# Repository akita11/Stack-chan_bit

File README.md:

# Stack-chan_bit

[ｽﾀｯｸﾁｬﾝ](https://protopedia.net/prototype/2345Stack-chan)に[micro:bit](https://www.switch-science.com/products/7952)を差し込んで制御するボードです。micro:bitのプログラミングでｽﾀｯｸﾁｬﾝを動かすことができます。

## 使用例

micro:bit側のプログラム（m-asaoka-fap氏作成の[カスタムブロック](https://github.com/m-asaoka-fap/stackchanbit_2)あり）から、ｽﾀｯｸﾁｬﾝを制御できます。→[使用例](https://twitter.com/akita11/status/1656496746321842176)

## 作り方

### 用意するもの

- M5Stack (BasicまたはCore2がオススメ)
- [Stack-chan_Takao_Base](https://github.com/akita11/Stack-chan_Takao_Base)とそれで用いるもの（サーボモータ2個、Groveケーブル、ネジ等、筐体(shell部以外)）※顔部分のM5Stack本体との固定には、BasicではM3x15mm、Core2ではM3x20mmのネジを2本使います
- shell部の筐体(Stack-chan_bit_shell.stlを3Dプリントしたもの): [タカオ版筐体](https://github.com/meganetaaan/stack-chan/tree/dev/v1.0/case/contributed/mongonta_case_for_SG90_and_M5GoBottomBoard/case_for_SG90andM5GoBottomBoard)内の”shell_SG90_basicgraybottom_v1.0.stl"を元に改変

### 組み立て

M5Stackに専用プログラム（FW_PIO/以下。PlatformIO用）を書き込みます。

M5Stackの底板を外し、Stack-chan_bitをさしこみます。

2本のM3ネジで固定します

[Stack-chan_Takao_Base](https://github.com/akita11/Stack-chan_Takao_Base)を使って
Bracket部（サーボ2個が固定される部分）を組み立てつつ、Stack-chan:bit基板と、Groveケーブルで接続します。

残りの部分は、Stack-chan_Takao_BaseからのGroveケーブルは、M5Stack本体ではなく、Stack-chan_bitのGroveコネクタに接続する

残りの部分は、[タカオさんの手順](https://raspberrypi.mongonta.com/how-to-build-easy-stackchan-m5gobottom/)を参考に組み立てます。

## プログラミング

micro:bitとｽﾀｯｸﾁｬﾝ(M5Stack)の間はUART通信(115200bps・N81、コマンド区切りはLF/0x0a/'\n'）で以下のような制御コマンドを送って制御します。[micro:bit側のカスタムブロック](https://github.com/m-asaoka-fap/stackchanbit_2)もあり、MakeCoreで組み込んで使用できます。

- 動作の制御
  - Xnn : パン動作（横方向）nn=角度、範囲＝-90〜90（正面=0）
  - Ynn : チルト動作（縦方向）nn=角度、範囲=0〜30（正面=0から上向きへ）
- 顔の制御
  - Txxxx : 吹き出しに”xxxx”と表示し、それにあわせて口が動く
  - En : 表情を設定。n=0〜5 (0=Angry, 1=Sleepy, 2=Happy, 3=Sat, 4=Doubt, 5=Neutral)

## （おまけ）拡張用Grove端子

M5Stackやmicro:bitの一部の端子をGrove端子に引き出せるようにGroveコネクタ実装部が用意してあります。詳細は回路図を参照してください。ただし使用する場合はGroveコネクタ部分にあわせて筐体(shell)の修正が必要になります。

## Author

Junichi Akita (@akita11, akita@ifdl.jp)

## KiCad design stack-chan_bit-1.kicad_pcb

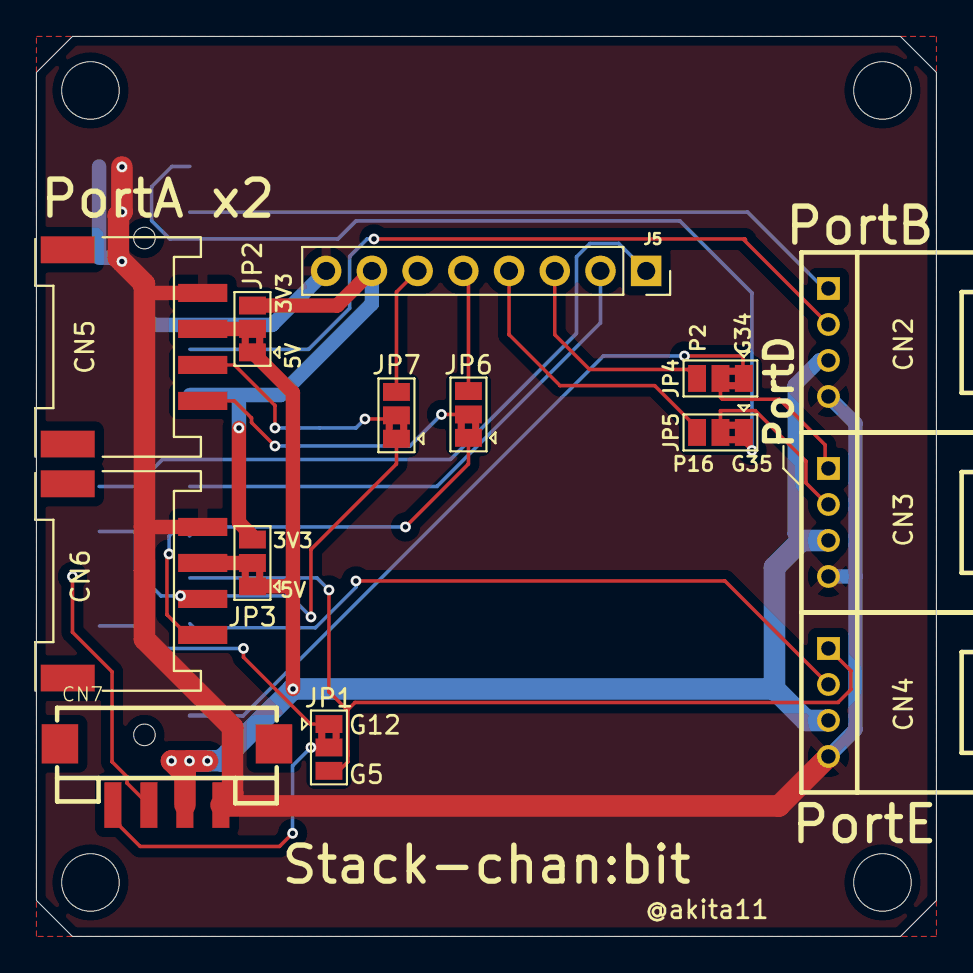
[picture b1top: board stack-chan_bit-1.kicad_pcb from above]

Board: 2 copper layers, 50.0 x 50.0 mm, 15 parts (1 on the bottom side), 26 nets.

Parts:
CN1: CON_MBUS_bottom; PinSocket_2x15_P2.54mm_Vertical_SMD
CN2, CN3, CN4: CON_GROVE; CON_GROVE_H
CN5, CN6: CON_GROVE; CON_GROVE_H_SMD
CN7: CON_GROVE; CON_GROVE_V_SMD
J5: Conn_01x08; PinSocket_1x08_P2.54mm_Vertical
JP1, JP2, JP3, JP4, JP5, JP6, JP7: SolderJumper_3_Bridged12; SolderJumper-3_P1.3mm_Bridged2Bar12_Pad1.0x1.5mm

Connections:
+3V3: CN1.12 (3V3), J5.7, JP2.3 (B), JP3.3 (B)
+5V: CN1.28 (5V), CN2.3, CN3.3, CN4.3, CN7.3, JP2.1 (A), JP3.1 (A)
/G5: CN1.20 (G5), CN4.1, JP1.3 (B)
/G12: CN1.21 (G12-ADC2-CH5), JP1.1 (A)
/G13: CN1.22 (G13-ADC2-CH4-T4), CN4.2
/G21: CN1.17 (G21-SDA), CN6.2, JP7.1 (A)
/G22: CN1.18 (G22-SCL), CN6.1, JP6.1 (A)
/G26: CN1.10 (G26-AD2-CH9), CN2.2
/G34: CN1.26 (G34-ADC1-CH6), JP4.1 (A)
/G35: CN1.2 (G35-ADC1-CH7), JP5.1 (A)
/G36: CN1.4 (G36-ADC1-CH0), CN2.1
/P0m: CN1.15 (G16-RXD2), J5.1
/P1m: CN1.16 (G17-TXD2), J5.2
/P2m: J5.3, JP4.3 (B)
/P16m: J5.4, JP5.3 (B)
/P19m: J5.5, JP6.3 (B)
/P20m: J5.6, JP7.3 (B)
/PA11: CN5.1, JP6.2 (C)
/PA12: CN5.2, JP7.2 (C)
/PD1: CN3.1, JP4.2 (C)
/PD2: CN3.2, JP5.2 (C)
/SV1: CN7.1, JP1.2 (C)
/SV2: CN1.19 (G2-ADC2-CH2-T2), CN7.2
/VDD-A1: CN5.3, JP2.2 (C)
/VDD-A2: CN6.3, JP3.2 (C)
GND: CN1.1 (GND), CN1.3 (GND1), CN1.5 (GND2), CN2.4, CN3.4, CN4.4, CN5.4, CN6.4, CN7.4, J5.8

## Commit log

2023-05-23 update shell stl
2023-05-24 update FW src
2023-05-24 update platformio.ini for Core2
2023-05-24 fix pin assignment for Core2
2023-06-01 update for product
2023-06-01 typo fix
2023-06-01 add README, optional Grove connector
